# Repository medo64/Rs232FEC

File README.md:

[RS-232 Framework Expansion Card](https://medo64.com/rs232framecard/)
=====================================================================

This Framework laptop expansion card will show up on your system as a serial
device and allow for a serial RS-232 communication up to 115,200 baud rate.

## RS-232 Pinout

To connect to this board, one has to use a 5-pin JST XH connector. The following
table represents the pinout, pin 1 being on the left as looking into the
expansion card.

| # | Ref | Description                     | DB9 | Sym |
|--:|:---:|---------------------------------|----:|:---:|
| 1 | CTS | Clear-to-send                   |  8  |  c  |
| 2 | RXD | Receive data                    |  2  |  R  |
| 3 | GND | Ground connection               |  5  |  ⏚  |
| 4 | TXD | Transmit data                   |  3  |  T  |
| 5 | RTS | Ready-to-send                   |  7  |  r  |

As power consumption is low, wires can be almost any AWG. I would recommend
using 24 AWG wire 0.25 mm² as they allow for greater compatibility with other
connectors.

## Supported Speeds

This board employs the FT232R as its UART chip, and consequently, it supports
all the baud rates this chip [can handle](https://ftdichip.com/Documents/AppNotes/AN232B-05_BaudRates.pdf)
up to 115,200 baud which is the limit of RS-232 chip used. The table below
lists the standard baud rates.

| Baud rate |    Actual | Error |    Divisor |
|----------:|----------:|------:|-----------:|
|       300 |       300 | 0.00% |  10000.000 |
|       600 |       600 | 0.00% |   5000.000 |
|     1,200 |     1,200 | 0.00% |   2500.000 |
|     1,800 |     1,800 | 0.00% |   1666.625 |
|     2,400 |     2,400 | 0.00% |   1250.000 |
|     4,800 |     4,800 | 0.00% |    625.000 |
|     7,200 |     7,201 | 0.01% |    416.625 |
|     9,600 |     9,600 | 0.00% |    312.500 |
|    14,400 |    14,406 | 0.04% |    208.250 |
|    19,200 |    19,200 | 0.00% |    156.250 |
|    28,800 |    28,812 | 0.04% |    104.125 |
|    38,400 |    38,400 | 0.00% |     78.125 |
|    57,600 |    57,692 | 0.16% |     52.000 |
|   115,200 |   115,385 | 0.16% |     26.000 |

---
*You can check my blog and other projects at [www.medo64.com](https://www.medo64.com/electronics/).*

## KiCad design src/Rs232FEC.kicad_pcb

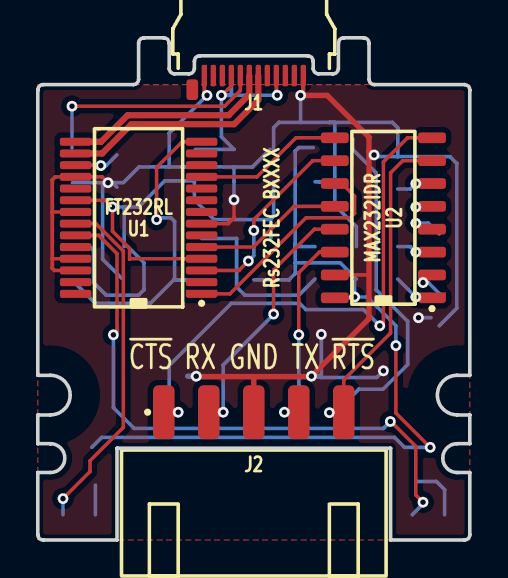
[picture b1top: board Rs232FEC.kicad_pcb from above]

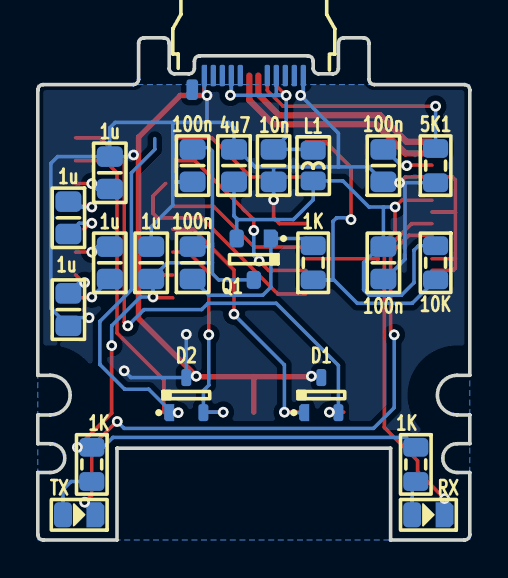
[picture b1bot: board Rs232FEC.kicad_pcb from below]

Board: 2 copper layers, 24.0 x 27.9 mm, 26 parts (22 on the bottom side), 28 nets.

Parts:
C1: 10n; C (0805)
C2, C3, C4, C5: 100n; C (0805)
C6, C7, C9, C9#2, C10: 1u; C (0805)
C6#2: 4u7; C (0805)
D1, D2: PESD12VL2BT; D TVS 12V [PESD12VL2BT,215] (SOT23-3)
DS1: RX; DS (0805)
DS2: TX; DS (0805)
J1: 105444-0001; J USB C 3.2 Edge (24w)
J2: B5B-XH-A; J JST XH Edge [RS232] (5w)
L1: 600R; L (0805)
Q1: DMP3099L-13; Q MOSFET-P (SOT23-3)
R1, R2, R3: 1K; R (0805)
R4: 5K1; R (0805)
R5: 10K; R (0805)
U1: FT232RL; U Transceiver UART [FT232R] (SSOP-28)
U2: MAX232IDR; U Transceiver RS232 [MAX232IDR] (SOIC-16)

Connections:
3V3: C3.2, U1.17
5V: C2.2, C6#2.2, L1.1, Q1.2, R5.1, U1.4, U1.20
5V_SW: C4.2, C5.2, C6.1, Q1.3, R1.1, R2.1, U2.16
A_CC: J1.A5, R4.2
C1+: C9#2.1, U2.1
C1-: C9#2.2, U2.3
C2+: C9.2, U2.4
C2-: C9.1, U2.5
CTS: U1.11, U2.9
GND: C1.1, C2.1, C3.1, C4.1, C6.2, C6#2.1, C7.2, C10.2, D1.3, D2.3, J1.A1, J1.A12, J1.B01, J1.B12, J2.3, R4.1, U1.7, U1.18, U1.21, U1.25, U1.26, U2.15
LED_RXD: DS1.1, U1.22
LED_RXD': DS1.2, R1.2
LED_TXD: DS2.1, U1.23
LED_TXD': DS2.2, R2.2
PWREN#: R3.1, R5.2, U1.14
PWREN#': C5.1, Q1.1, R3.2
RS232_CTS: D1.2, J2.1, U2.8
RS232_RTS: D2.1, J2.5, U2.7
RS232_RX: D1.1, J2.2, U2.13
RS232_TX: D2.2, J2.4, U2.14
RTS: U1.3, U2.10
RXD: U1.5, U2.12
TXD: U1.1, U2.11
USB_DM: J1.A7, U1.16
USB_DP: J1.A6, U1.15
USB_Vin: C1.2, J1.A4, J1.A9, J1.B04, J1.B09, L1.2
VS+: C10.1, U2.2
VS-: C7.1, U2.6

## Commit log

2022-04-16 Minor refactoring
2022-04-18 Moving LEDs to corner
2022-04-20 Updated pinout to RXD GND TXD
2022-04-21 Refactoring
2022-04-23 Adjusted shoulder
2022-05-06 Fixed via too close
2022-05-06 Fixed font not to use condensed variant
2022-05-07 Longer pads on type-C connector
2022-05-07 Removed extra CC2 resistor
2022-05-09 Turning LEDs around
2022-05-09 Updated case STLs
2022-05-13 Shorter screw
2022-05-13 Updated case files
2022-05-15 Add schematics
2022-06-21 Updated project repo name
2023-11-03 Reworked in KiCAD with FT232R
2023-11-04 Added RTS/CTS loopback
2023-11-13 Changed protection diode
2023-11-13 Minor refactorings
2023-11-13 Moved LEDs to bottom
2023-12-26 Added PWREN pullup and moved LED 5V to switched
2023-12-26 Changed connector to include CTS/RTS lines
2023-12-26 Moved LED resistors to bottom
2023-12-30 Refactoring copper pour
2024-01-06 Added DB-9 pinout
2024-01-31 Moved board RefDes to top
2024-04-02 Updated connector designators
2025-08-01 Updated board RefDes
2025-08-01 Cleaning up components
2025-08-26 Updated footprints
2025-09-28 Increased cap rating
2025-09-28 Added symbols
2025-09-28 CD is on by default
2025-09-29 Updated 3D models
2025-09-29 No signal inversion config
2025-09-29 Swapped CTS and RTS. Doh!
